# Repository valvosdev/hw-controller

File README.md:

# Aqua:eq8

> Open Hardware. Open Source. Smart Irrigation.

Aqua:eq8 is an open-source and open-hardware 8-zone smart irrigation controller designed for residential, commercial, greenhouse, and agricultural installations.

Built around the ESP32-C3-MINI-N4, Aqua:eq8 combines reliable irrigation control with secure connectivity, mobile management, OTA firmware updates, MQTT communication, and cloud integration while remaining fully self-hostable and hackable.

The project includes:

- ESP32 firmware
- Hardware schematics and PCB design
- Golang backend API
- React Native mobile application
- Docker, Kubernetes, and Helm deployment support

---

## Features

### Irrigation Control

- 8 independent irrigation zones
- Multiple zones can run simultaneously
- Configurable Master Valve support
- Configurable pump start delay
- Local manual operation without Internet
- Mobile application control
- MQTT-based communication
- Future scheduling support
- Future weather integration
- Emergency stop functionality

### Connectivity

- WiFi provisioning via BLE
- Bluetooth Low Energy onboarding
- MQTT communication
- OTA firmware updates
- Cloud synchronization
- Device telemetry

### Security

- ESP32 Secure Boot
- Flash Encryption
- Signed OTA updates
- TLS communication
- Device authentication
- Secure credential storage

### Reliability

- Offline-first operation
- Local control during Internet outages
- Hardware watchdog
- Software watchdog
- Automatic recovery
- Power-loss recovery

### Open Source

- Open firmware
- Open hardware
- Open API
- Open mobile app
- Self-hostable backend

---

# Repository Structure

text aqua-eq8/ ├── firmware/ │   ├── main/ │   ├── components/ │   ├── ble/ │   ├── wifi/ │   ├── mqtt/ │   ├── ota/ │   └── valve/ │ ├── hardware/ │   ├── schematic/ │   ├── pcb/ │   ├── enclosure/ │   └── bom/ │ ├── api/ │   ├── cmd/ │   ├── internal/ │   ├── deployments/ │   ├── helm/ │   └── docker/ │ ├── mobile/ │   ├── src/ │   ├── ios/ │   └── android/ │ └── docs/ 

---

# Hardware

## Power

The controller is powered by a standard irrigation transformer.

### Input

text 24VAC Barrel Jack 

### Internal Rails

text 24VAC  ├── Valve Outputs  ├── Current Monitoring  └── AC/DC Converter       ├── 5V       └── 3.3V 

---

## Main Components

### MCU

- ESP32-C3-MINI-N4
- WiFi 2.4GHz
- Bluetooth Low Energy
- 4MB Flash

### Output Expansion

Two 74HC595 shift registers are used:

#### Shift Register #1

Controls:

- 8 TRIAC outputs
- 8 Green status LEDs

#### Shift Register #2

Controls:

- 8 Red Master LEDs

This minimizes GPIO usage while allowing future expansion.

### Valve Drivers

- TRIAC-based switching
- Designed for 24VAC sprinkler valves
- RC snubber protection per channel
- Future current sensing support

### Protection

- Input fuse
- Snubber protection on every channel
- Brownout protection
- Hardware watchdog
- Secure boot
- Flash encryption

---

# Channel Controls

## Channels 1-8

Each button controls one irrigation zone.

### Short Press

Toggle zone state.

| Current State | Action |
|--------------|----------|
| OFF | Turn ON |
| ON | Turn OFF |

### Long Press

Toggle Master Valve assignment.

| Current State | Action |
|--------------|----------|
| Normal Zone | Set as Master |
| Master Zone | Remove Master |

Only one channel may be configured as Master at a time.

---

# Master Valve Operation

A Master Valve is commonly used for:

- Main water supply
- Pump control
- Pressure system enable

When any non-master zone is enabled:

1. Master Valve turns ON immediately
2. Zone enters waiting state
3. Configurable delay timer starts
4. Zone activates after delay

Example:

text Channel 1 = Master  User enables Channel 3  Channel 1 ON immediately  Channel 3 LED flashes  5 second delay  Channel 3 ON 

When the last active zone stops:

text Channel 3 OFF  No active zones remaining  Channel 1 OFF 

### Default Delay

yaml master_delay_seconds: 5 

Configurable through the mobile application.

---

# Channel LED Behavior

Each channel button contains:

- Green LED
- Red LED

## Green LED

Indicates operational state.

| State | Green |
|---------|---------|
| OFF | OFF |
| Waiting Master Delay | Flashing |
| Active | Solid |

## Red LED

Indicates configuration state.

| State | Red |
|---------|---------|
| Normal Zone | OFF |
| Master Zone | Solid |

## Combined States

| State | Green | Red |
|---------|---------|---------|
| OFF | OFF | OFF |
| ON | ON | OFF |
| Master OFF | OFF | ON |
| Master ON | ON | ON |
| Waiting Delay | Flashing | OFF |

---

# Status Button (Button 9)

Button 9 is a dedicated RGB status and management button.

Functions:

- Device Status
- BLE Pairing
- Factory Reset

---

## RGB Status LED

The status LED always displays the highest priority state.

Priority:

text Error OTA Update BLE Connected BLE Advertising WiFi Connected Booting 

### States

| State | RGB |
|---------|---------|
| Booting | White Breathing |
| WiFi Connected | Solid Green |
| BLE Advertising | Blue Breathing |
| Mobile App Connected | Solid Blue |
| OTA Update | Purple Breathing |
| Error | Red Flashing |

---

## Button Actions

### Short Press

Enable BLE pairing mode.

LED:

text Blue Breathing 

Duration:

text 10 Minutes 

### Long Press (10 Seconds)

Factory Reset.

Deletes:

- WiFi Credentials
- MQTT Configuration
- Device Pairing
- Local Configuration
- Schedules

LED:

text Red Breathing 

Device automatically reboots.

---

# Connectivity

Aqua:eq8 intentionally avoids:

- Captive Portals
- Access Point Setup
- Embedded Web UI

All device provisioning is performed through Bluetooth Low Energy.

### Provisioning Flow

text Power Device       ↓ Press Status Button       ↓ BLE Pairing       ↓ Mobile App       ↓ Send WiFi Credentials       ↓ Connect to Network       ↓ Register with Backend       ↓ MQTT Connected 

---

# MQTT

MQTT is the primary communication mechanism between the controller and backend services.

## Topics

text aquaeq8/{deviceId}/state aquaeq8/{deviceId}/events aquaeq8/{deviceId}/telemetry aquaeq8/{deviceId}/command aquaeq8/{deviceId}/ota 

## Example Telemetry

json {   "uptime": 86400,   "wifi_rssi": -62,   "free_heap": 124832,   "active_zones": [2,4,7] } 

MQTT data can be consumed directly by:

- Telegraf
- InfluxDB
- TimescaleDB
- VictoriaMetrics
- Grafana

---

# Firmware

Location:

text /firmware 

Built using:

- ESP-IDF
- FreeRTOS
- C/C++

## Features

### Device Control

- Zone management
- Master Valve logic
- Delay handling
- Local operation

### Connectivity

- BLE provisioning
- WiFi management
- MQTT client

### OTA

- Signed firmware updates
- Rollback protection
- Secure update process

### Security

- Secure Boot
- Flash Encryption
- Device authentication

### Reliability

- Hardware watchdog
- Software watchdog
- Crash recovery

---

# Backend API

Location:

text /api 

Built using:

- Go 1.26+
- PostgreSQL
- Redis
- MQTT

## Features

### Device Management

- Device registration
- Pairing
- Configuration synchronization

### Monitoring

- Online/offline status
- Telemetry collection
- Device diagnostics

### Security

- JWT authentication
- TLS communication
- API rate limiting

---

# Deployment

## Docker

bash docker compose up -d 

## Kubernetes

bash kubectl apply -f deployments/ 

## Helm

bash helm install aquaeq8 ./helm 

---

# Mobile Application

Location:

text /mobile 

Built using:

- React Native
- TypeScript

## Features

### Device Setup

- BLE discovery
- WiFi provisioning
- Device pairing

### Device Management

- Zone control
- Master Valve configuration
- Delay configuration

### Monitoring

- Device health
- Connectivity status
- Telemetry visualization

### OTA

- Firmware update notifications
- Update progress monitoring

---

# Future Features

## Planned

- Irrigation schedules
- Weather integration
- Rain delay
- Seasonal adjustments
- Water usage analytics

## Hardware Expansion

- Flow meter support
- Rain sensor input
- Valve current monitoring
- Leak detection
- Pump monitoring

---

# Valve Current Monitoring

Future versions may include electrical current sensing on each output channel.

Benefits:

- Detect disconnected valves
- Detect broken wires
- Detect short circuits
- Detect stuck valves
- Improve diagnostics

Example:

text Zone 4 ON  Expected Current: 220mA Measured Current: 0mA  Alert: Valve Not Connected 

---

# Development

## Firmware

bash cd firmware  idf.py build idf.py flash idf.py monitor 

## Backend

bash cd api  go run ./cmd/server 

## Mobile

bash cd mobile  yarn install yarn start 

---

# Security Model

Every controller includes:

- Unique Device ID
- Device Certificate
- Private Key

Firmware security:

- Secure Boot enabled
- Flash Encryption enabled
- Signed OTA updates only

The controller never accepts unsigned firmware images.

---

# Contributing

Contributions are welcome.

Areas where help is needed:

- Embedded development
- Hardware design
- Backend development
- Mobile development
- Testing
- Documentation

Please open an issue or submit a pull request.

---

# License

MIT License

See LICENSE for details.

---

# Philosophy

Aqua:eq8 is built around three principles.

## Open Source

All software is publicly available.

## Open Hardware

PCB layouts and schematics are publicly available.

## Local First

Your irrigation system continues operating even if the Internet does not.

---

Aqua:eq8

An open-source, secure, MQTT-native irrigation controller built for modern gardens, farms, and greenhouses.

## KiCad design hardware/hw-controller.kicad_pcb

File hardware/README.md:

# Branch hw-cnt-v1.0.1
this branch is for fixing the issues from hw-cnt-v1.0.0

# TODO
1. C12 make thoughhole
2. Change BT triac to something smaller and cheaper
3. 

As a development pcb it can be used as issues above can be fixed.

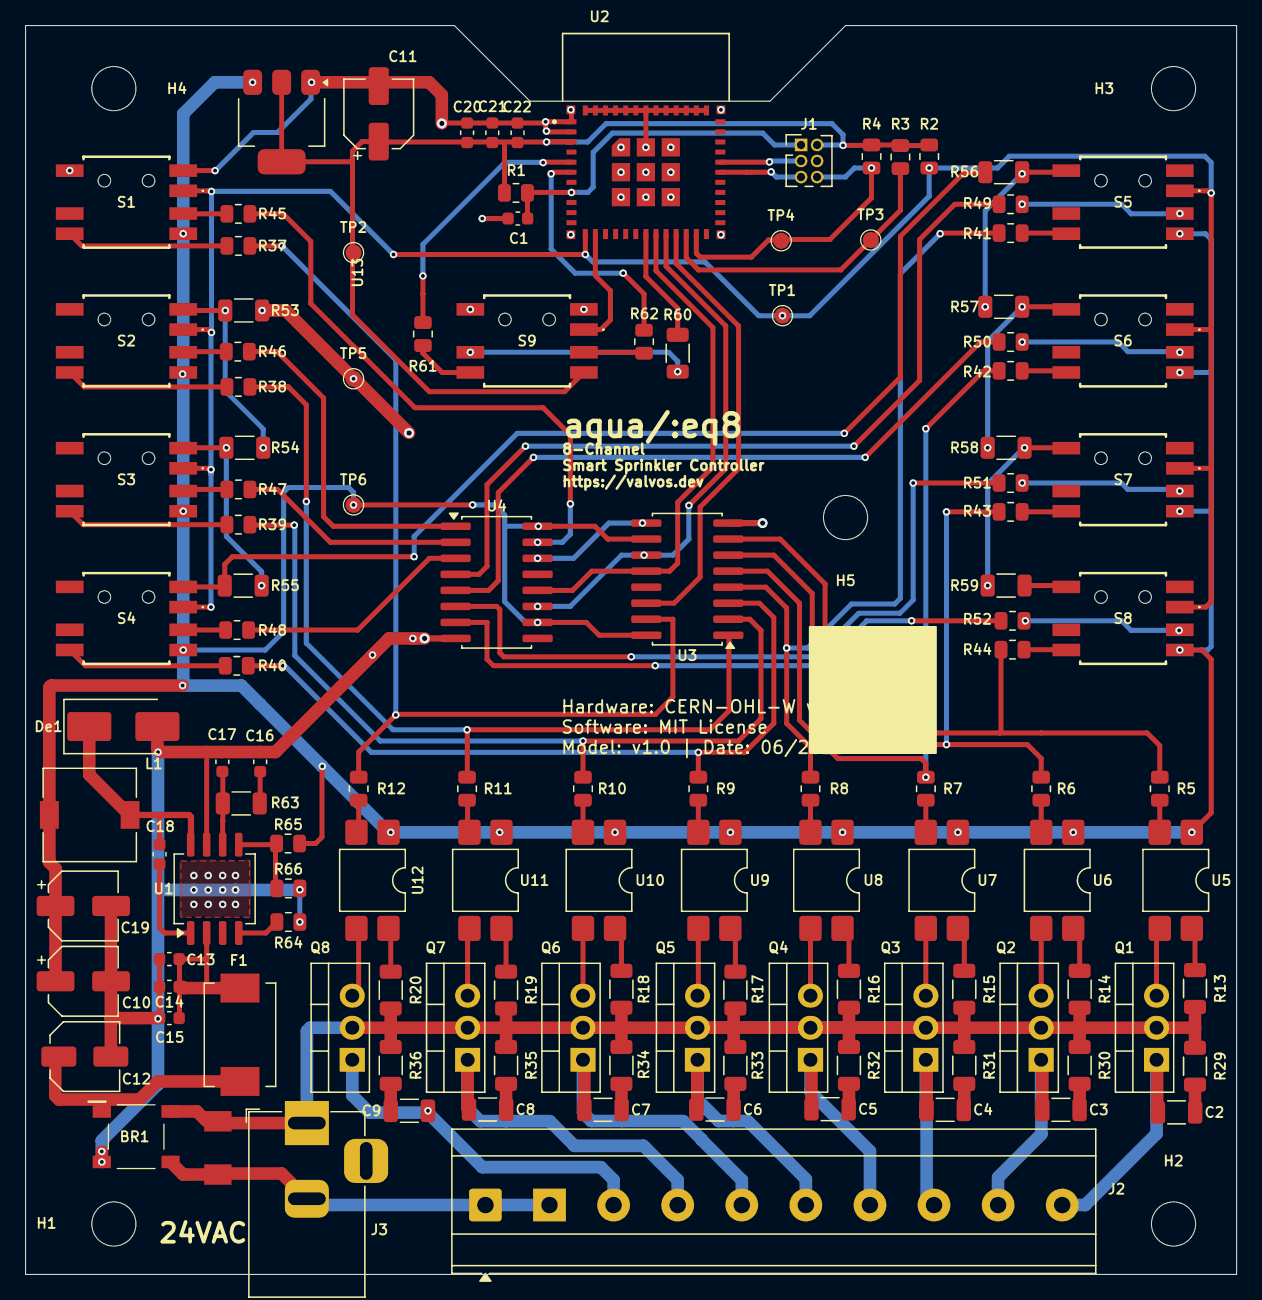
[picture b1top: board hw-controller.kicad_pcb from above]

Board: 2 copper layers, 96.0 x 99.0 mm, 129 parts (0 on the bottom side), 109 nets.

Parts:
BR1: ABS10A-13; ABS10A13
C1, C22: 1uF; C_0603_1608Metric
C2, C3, C4, C5, C6, C7, C8, C9: 10nF; C_1206_3216Metric
C10, C11: 10uF; CP_Elec_5x5.7
C12: 330uF; C_Elec_5x5.8
C13, C14: 2.2uF; C_0603_1608Metric
C15, C18, C21: 0.1uF; C_0603_1608Metric
C16: 5.6nF; C_0603_1608Metric
C17: 100pF; C_0603_1608Metric
C19: 47uF; CP_Elec_5x5.7
C20: 10uF; C_0603_1608Metric
D1: D_TVS_Small_Filled; DO-214AA
De1: B360A-13-F; D_SMB_Handsoldering
F1: Fuse; Fuse_Bourns_MF-SM_7.98x5.44mm
H1, H2, H3, H4, H5: MH; MountingHole_3.5mm
J1: Conn_02x03_Odd_Even; PinHeader_2x03_P1.27mm_Vertical
J2: Conn_01x10; TerminalBlock_Phoenix_MKDS-3-10-5.08_1x10_P5.08mm_Horizontal
J3: Jack-DC; BarrelJack_Horizontal
L1: 15uH; L_7.3x7.3_H4.5
Q1, Q2, Q3, Q4, Q5, Q6, Q7, Q8: BT136-500; TO-220-3_Vertical
R1, R2, R3, R4, R66: 10k; R_0805_2012Metric
R5, R6, R7, R8, R9, R10, R11, R12, R61, R62: 470; R_0805_2012Metric
R13, R14, R15, R16, R17, R18, R19, R20: 330; R_1206_3216Metric
R29, R30, R31, R32, R33, R34, R35, R36, R60: 160; R_1206_3216Metric
R37, R38, R39, R40, R41, R42, R43, R44, R45, R46, R47, R48, R49, R50, R51, R52: 1k; R_0805_2012Metric
R53, R54, R55, R56, R57, R58, R59: 1.8k; R_1206_3216Metric
R63: 7k5; R_1206_3216Metric
R64: 392k; R_0805_2012Metric
R65: 51k; R_0805_2012Metric
S1: RGBFR_CH1; 228EMVARGBFR
S2: RGBFR_CH2; 228EMVARGBFR
S3: RGBFR_CH3; 228EMVARGBFR
S4: RGBFR_CH4; 228EMVARGBFR
S5: RGBFR_CH5; 228EMVARGBFR
S6: RGBFR_CH6; 228EMVARGBFR
S7: RGBFR_CH7; 228EMVARGBFR
S8: RGBFR_CH8; 228EMVARGBFR
S9: RGBFR_STATUS; 228EMVARGBFR
TP1, TP2, TP3, TP4, TP5, TP6: TP_1_27
U1: RT6362GSP; SOIC-8_5.3x6.2mm_P1.27mm
U2: ESP32-C3-MINI-1-N4; XCVR_ESP32-C3-MINI-1-N4
U3, U4: 74HC595; SOIC-16W_5.3x10.2mm_P1.27mm
U5, U6, U7, U8, U9, U10, U11, U12: FODM3053; SMDIP-4_W7.62mm
U13: AMS1117-3.3; SOT-223-3_TabPin2

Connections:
+3.3V: C11.1, C20.1, C21.1, C22.1, J1.2, R1.1, R2.1, R3.1, R4.1, S9.L1 (COM_A), TP2.1 (TP_1), U2.3 (3V3), U13.2 (VO)
+5V: C10.1, C19.1, L1.2, R65.2, S1.L1 (COM_A), S2.L1 (COM_A), S3.L1 (COM_A), S4.L1 (COM_A), S5.L1 (COM_A), S6.L1 (COM_A), S7.L1 (COM_A), S8.L1 (COM_A), TP6.1 (TP_1), U3.10 (~SRCLR), U3.16 (VCC), U4.10 (~SRCLR), U4.16 (VCC), U5.1, U6.1, U7.1, U8.1, U9.1, U10.1, U11.1, U12.1, U13.3 (VI)
/24VAC1: BR1.2 (~_1), D1.2 (A2), J3.1, Q1.2 (A2), Q2.2 (A2), Q3.2 (A2), Q4.2 (A2), Q5.2 (A2), Q6.2 (A2), Q7.2 (A2), Q8.2 (A2), R13.2, R14.2, R15.2, R16.2, R17.2, R18.2, R19.2, R20.2, R29.1, R30.1, R31.1, R32.1, R33.1, R34.1, R35.1, R36.1
/24VAC2: BR1.4 (~_2), D1.1 (A1), J2.1, J2.2, J3.2
BTNS_PIN: R2.2, S1.A1 (COM), S2.A1 (COM), S3.A1 (COM), S4.A1 (COM), S5.A1 (COM), S6.A1 (COM), S7.A1 (COM), S8.A1 (COM), TP1.1 (TP_1), U2.12 (IO0)
EN: C1.1, J1.1, R1.2, U2.8 (EN)
GND: BR1.3 (-), C1.2, C10.2, C11.2, C12.2, C13.2, C14.2, C15.2, C16.1, C17.1, C19.2, C20.2, C21.2, C22.2, De1.2 (A), J1.4, R53.2, R64.1, R66.1, S1.B1 (NO_1), S1.B2 (NO_2), S9.B1 (NO_1), S9.B2 (NO_2), TP5.1 (TP_1), U1.7 (GND), U2.1 (GND), U2.2 (GND), U2.11 (GND), U2.14 (GND), U2.36 (GND), U2.37 (GND), U2.38 (GND), U2.39 (GND), U2.40 (GND), U2.41 (GND), U2.42 (GND), U2.43 (GND), U2.44 (GND), U2.45 (GND), U2.46 (GND), U2.47 (GND), U2.48 (GND), U2.49_1 (GND), U2.49_2 (GND), U2.49_3 (GND), U2.49_4 (GND), U2.49_5 (GND), U2.49_6 (GND), U2.49_7 (GND), U2.49_8 (GND), U2.49_9 (GND), U2.50 (GND), U2.51 (GND), U2.52 (GND), U2.53 (GND), U3.8 (GND), U4.8 (GND), U13.1 (GND)
LATCH: U2.19 (IO5), U3.12 (RCLK), U4.12 (RCLK)
LEDG_CH1: R45.2, U4.15 (QA)
LEDG_CH2: R46.2, U4.1 (QB)
LEDG_CH3: R47.2, U4.2 (QC)
LEDG_CH4: R48.2, U4.3 (QD)
LEDG_CH5: R49.2, U4.4 (QE)
LEDG_CH6: R50.2, U4.5 (QF)
LEDG_CH7: R51.2, U4.6 (QG)
LEDG_CH8: R52.2, U4.7 (QH)
LEDR_CH1: R12.1, R37.1, U3.15 (QA)
LEDR_CH2: R11.1, R38.1, U3.1 (QB)
LEDR_CH3: R10.1, R39.1, U3.2 (QC)
LEDR_CH4: R9.1, R40.1, U3.3 (QD)
LEDR_CH5: R8.1, R41.1, U3.4 (QE)
LEDR_CH6: R7.1, R42.1, U3.5 (QF)
LEDR_CH7: R6.1, R43.1, U3.6 (QG)
LEDR_CH8: R5.1, R44.1, U3.7 (QH)
unnamed: BR1.1 (+), C12.1, F1.1
unnamed: C2.1, R29.2
unnamed: C3.1, R30.2
unnamed: C4.1, R31.2
unnamed: C5.1, R32.2
unnamed: C6.1, R33.2
unnamed: C7.1, R34.2
unnamed: C8.1, R35.2
unnamed: C9.1, R36.2
unnamed: C16.2, R63.1
unnamed: C18.2, De1.1 (K), L1.1, U1.8 (SW)
unnamed: C9.2, J2.3, Q8.1 (A1)
unnamed: C8.2, J2.4, Q7.1 (A1)
unnamed: C7.2, J2.5, Q6.1 (A1)
unnamed: C6.2, J2.6, Q5.1 (A1)
unnamed: C5.2, J2.7, Q4.1 (A1)
unnamed: C4.2, J2.8, Q3.1 (A1)
unnamed: C3.2, J2.9, Q2.1 (A1)
unnamed: C2.2, J2.10, Q1.1 (A1)
unnamed: Q1.3 (G), U5.3
unnamed: Q2.3 (G), U6.3
unnamed: Q3.3 (G), U7.3
unnamed: Q4.3 (G), U8.3
unnamed: Q5.3 (G), U9.3
unnamed: Q6.3 (G), U10.3
unnamed: Q7.3 (G), U11.3
unnamed: Q8.3 (G), U12.3
unnamed: R5.2, U5.2
unnamed: R6.2, U6.2
unnamed: R7.2, U7.2
unnamed: R8.2, U8.2
unnamed: R9.2, U9.2
unnamed: R10.2, U10.2
unnamed: R11.2, U11.2
unnamed: R12.2, U12.2
unnamed: R13.1, U5.4
unnamed: R14.1, U6.4
unnamed: R15.1, U7.4
unnamed: R16.1, U8.4
unnamed: R17.1, U9.4
unnamed: R18.1, U10.4
unnamed: R19.1, U11.4
unnamed: R20.1, U12.4
unnamed: R45.1, S1.L2 (K_GREEN)
unnamed: R37.2, S1.L3 (K_RED)
unnamed: R46.1, S2.L2 (K_GREEN)
unnamed: R38.2, S2.L3 (K_RED)
unnamed: R53.1, R54.2, S2.B1 (NO_1), S2.B2 (NO_2)
unnamed: R47.1, S3.L2 (K_GREEN)
unnamed: R39.2, S3.L3 (K_RED)
unnamed: R54.1, R55.2, S3.B1 (NO_1), S3.B2 (NO_2)
unnamed: R48.1, S4.L2 (K_GREEN)
unnamed: R40.2, S4.L3 (K_RED)
unnamed: R55.1, R56.2, S4.B1 (NO_1), S4.B2 (NO_2)
unnamed: R49.1, S5.L2 (K_GREEN)
unnamed: R41.2, S5.L3 (K_RED)
unnamed: R56.1, R57.2, S5.B1 (NO_1), S5.B2 (NO_2)
unnamed: R50.1, S6.L2 (K_GREEN)
unnamed: R42.2, S6.L3 (K_RED)
unnamed: R57.1, R58.2, S6.B1 (NO_1), S6.B2 (NO_2)
unnamed: R51.1, S7.L2 (K_GREEN)
unnamed: R43.2, S7.L3 (K_RED)
unnamed: R58.1, R59.2, S7.B1 (NO_1), S7.B2 (NO_2)
unnamed: R52.1, S8.L2 (K_GREEN)
unnamed: R44.2, S8.L3 (K_RED)
unnamed: R59.1, S8.B1 (NO_1), S8.B2 (NO_2)
unnamed: R60.2, S9.L4 (K_BLUE)
unnamed: R62.1, S9.L2 (K_GREEN)
unnamed: R61.2, S9.L3 (K_RED)
unnamed: C18.1, U1.1 (BOOT)
unnamed: C17.2, R63.2, U1.6 (COMP)
unnamed: R65.1, R66.2, U1.5 (FB)
unnamed: R64.2, U1.4 (RT/SYNC)
unnamed: C13.1, C14.1, C15.1, F1.2, U1.2 (VIN)
unnamed: U3.9 (QH'), U4.14 (SER)
RX: J1.5, U2.30 (RXD0)
SCL: J1.6, R4.2, TP4.1 (TP_1), U2.23 (IO9)
SDA: R3.2, TP3.1 (TP_1), U2.22 (IO8)
SIPO_DATA: U2.21 (IO7), U3.14 (SER)
SIPO_SCK: U2.20 (IO6), U3.11 (SRCLK), U4.11 (SRCLK)
STATUS_BTN_PIN: S9.A1 (COM), U2.13 (IO1)
STATUS_LEDB_PIN: R60.1, U2.18 (IO4)
STATUS_LEDG_PIN: R62.2, U2.6 (IO3)
STATUS_LEDR_PIN: R61.1, U2.5 (IO2)
TX: J1.3, U2.31 (TXD0)

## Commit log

2026-06-06 first implementation. There are some bugs and issues with the schematic. as development board this can work, NOT FOR PROD
2026-06-06 added Readme.md for hardware
2026-06-06 added project folder structure
2026-06-06 started branch v1.0.1
2026-06-06 added readme
2026-06-06 fix some minor markdown issues
2026-06-06 development branch

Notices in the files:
hardware/hw-controller.kicad_pcb:
Hardware: CERN-OHL-W v2
Software: MIT License
